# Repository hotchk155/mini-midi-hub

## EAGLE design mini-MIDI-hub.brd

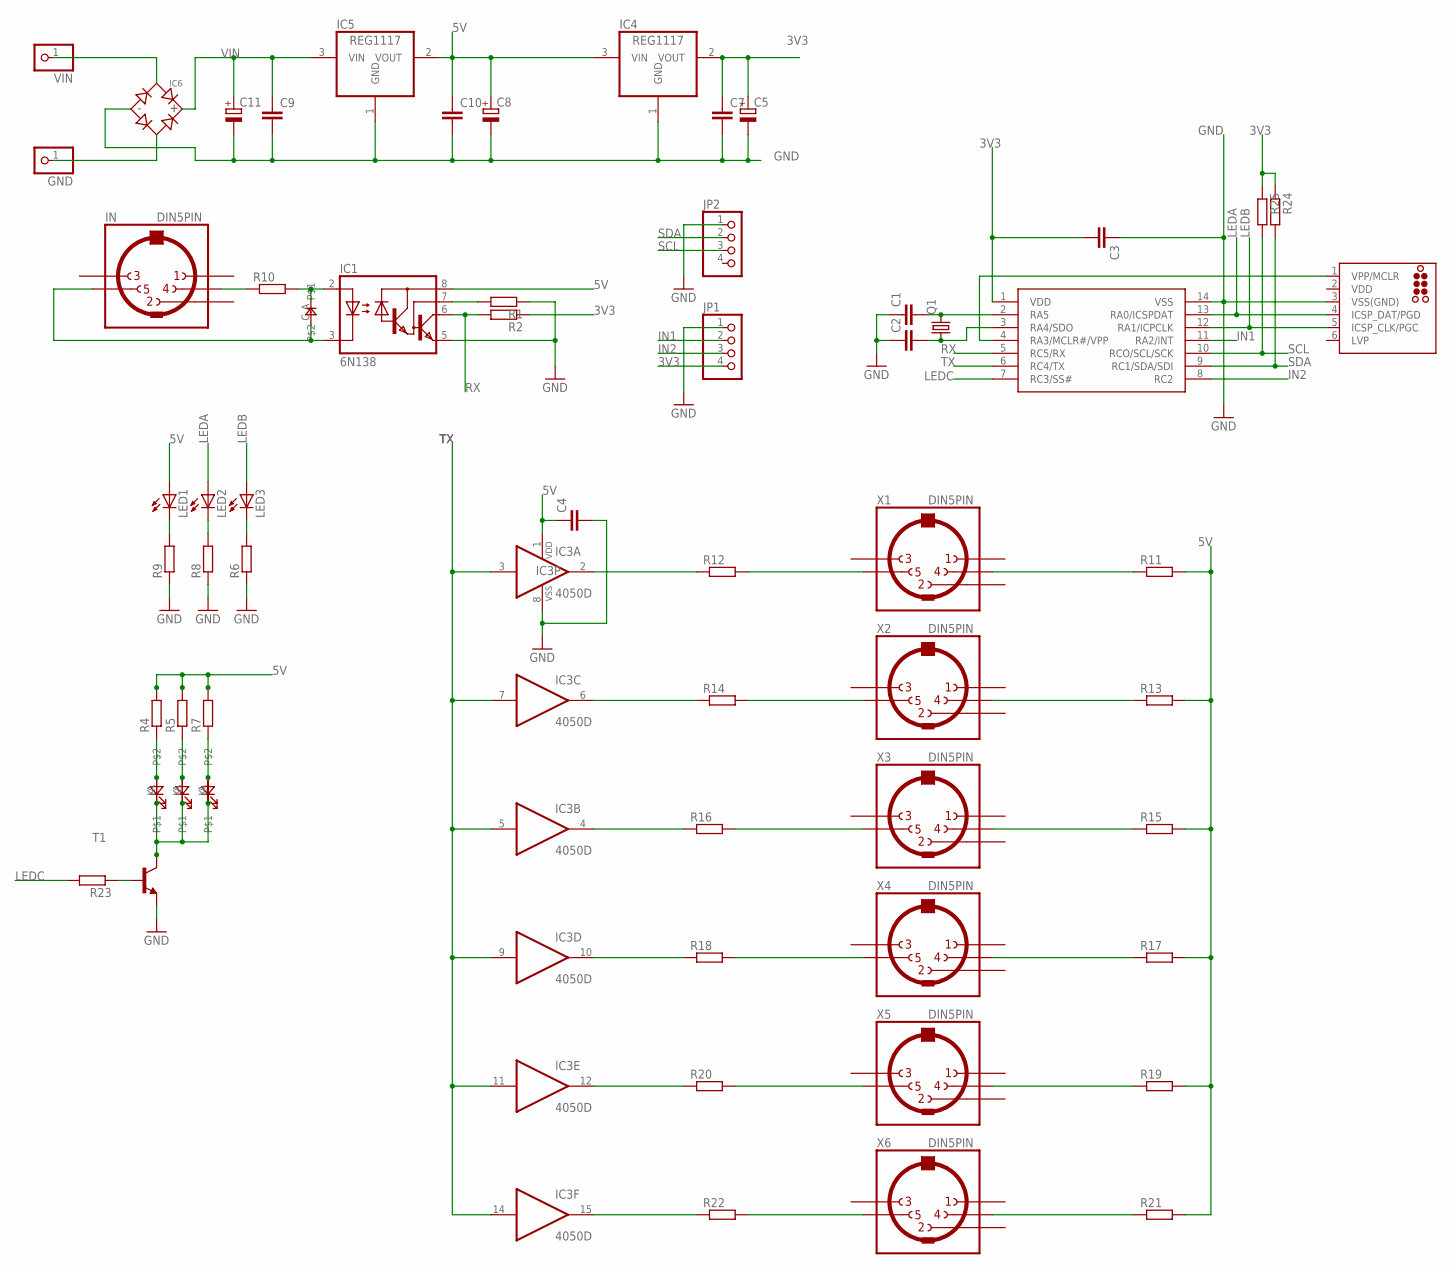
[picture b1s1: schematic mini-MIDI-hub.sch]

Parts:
C1, C2, C3, C4, C7, C9, C10: C-EUC0805; C0805
C5, C8, C11: CPOL-EUE2-4; E2-4
D1: 0805DIODE
GND: PINHD-1X1; 1X01
IC1: 6N138; DIL08
IC2: PIC16F1825SO14; SO14
IC3: 4050D; SO16
IC4, IC5: REG1117; SOT223
IC6: BRIDGERECTIFIER; SOIC-4
ICSP: TC2030-MCP-NL
IN: DIN5PIN; EDGEDIN
JP1, JP2: PINHD-1X4; 1X04
LED1, LED2, LED3: LED3MM
Q1: CRYSTALHC49S; HC49/S
R1, R2, R4, R5, R6, R7, R8, R9, R10, R11, R12, R13, R14, R15, R16, R17, R18, R19, R20, R21, R22, R23, R24, R25: R-EU_R0805; R0805
T1: MMBT3904LT1-NPN-SOT23-BEC; SOT23-BEC
U$2, U$3, U$4: LED5MM_EDGE
VIN: PINHD-1X1; 1X01
X1, X2, X3, X4, X5, X6: DIN5PIN; EDGEDIN

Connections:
3V3: C3.2, C5.+, C7.1, IC2.1 (VDD), IC4.2 (VOUT), JP1.4, R2.1, R24.1, R25.1
5V: C4.1, C8.+, C10.1, IC1.8 (VCC), IC3.1 (VDD), IC4.3 (VIN), IC5.2 (VOUT), LED1.A, R4.2, R5.2, R7.2, R11.2, R13.2, R15.2, R17.2, R19.2, R21.2
GND: C1.1, C2.1, C3.1, C4.2, C5.-, C7.2, C8.-, C9.2, C10.2, C11.-, IC1.5 (GND), IC2.14 (VSS), IC3.8 (VSS), IC4.1 (GND), IC5.1 (GND), IC6.-, ICSP.3 (VSS(GND)), JP1.1, JP2.1, R1.1, R6.1, R8.1, R9.1, T1.E
IN1: IC2.11 (RA2/INT), JP1.2
IN2: IC2.8 (RC2), JP1.3
LEDA: IC2.13 (RA0/ICSPDAT), ICSP.4 (ICSP_DAT/PGD), LED2.A
LEDB: IC2.12 (RA1/ICPCLK), ICSP.5 (ICSP_CLK/PGC), LED3.A
LEDC: IC2.7 (RC3/SS#), R23.2
unnamed: R12.2, X1.5
unnamed: R14.2, X2.5
unnamed: R16.2, X3.5
unnamed: R18.2, X4.5
unnamed: R20.2, X5.5
unnamed: R22.2, X6.5
unnamed: IC3.15 (O), R22.1
unnamed: IC3.4 (O), R16.1
unnamed: IC3.12 (O), R20.1
unnamed: IC3.10 (O), R18.1
unnamed: IC3.6 (O), R14.1
unnamed: IC3.2 (O), R12.1
unnamed: LED2.K (C), R8.2
unnamed: R11.1, X1.4
unnamed: R13.1, X2.4
unnamed: R15.1, X3.4
unnamed: R17.1, X4.4
unnamed: R19.1, X5.4
unnamed: R21.1, X6.4
unnamed: IN.4, R10.1
unnamed: D1.A, IC1.2 (A), R10.2
unnamed: IC1.7 (VB), R1.2
unnamed: LED1.K (C), R9.2
unnamed: D1.C, IC1.3 (C), IN.5
unnamed: LED3.K (C), R6.2
unnamed: R4.1, U$2.A
unnamed: IC6.~1 (AC1), VIN.1
unnamed: GND.1, IC6.~2 (AC2)
unnamed: C1.2, IC2.2 (RA5), Q1.2
unnamed: C2.2, IC2.3 (RA4/SDO), Q1.1
unnamed: R5.1, U$3.A
unnamed: R7.1, U$4.A
unnamed: T1.C, U$2.K, U$3.K, U$4.K
unnamed: IC2.4 (RA3/MCLR#/VPP), ICSP.1 (VPP/MCLR)
unnamed: R23.1, T1.B
RX: IC1.6 (VO), IC2.5 (RC5/RX), R2.2
SCL: IC2.10 (RCO/SCL/SCK), JP2.3, R25.2
SDA: IC2.9 (RC1/SDA/SDI), JP2.2, R24.2
TX: IC2.6 (RC4/TX), IC3.3 (I), IC3.5 (I), IC3.7 (I), IC3.9 (I), IC3.11 (I), IC3.14 (I)
VDD: ICSP.2 (VDD)
VIN: C9.1, C11.+, IC5.3 (VIN), IC6.+

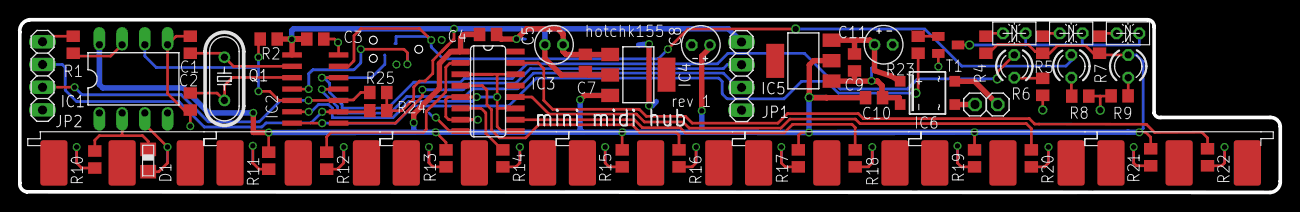
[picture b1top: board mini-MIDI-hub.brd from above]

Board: 2 copper layers, 140.9 x 19.3 mm, 61 parts (1 on the bottom side), 48 nets.

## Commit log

2015-11-21 :space_invader: Added .gitattributes & .gitignore files
2015-11-21 getting starter
2015-11-21 tweakz
2015-11-25 tweaks
2015-11-26 pcb rev 1

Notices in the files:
parts and their libraries:
tag-connect: ©2009 ROFA.cz - modified and updated by Robert Darlington ‹rdarlington@gmail.com›
